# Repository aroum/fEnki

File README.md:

# fEnki  
fEnki is an open source (free) version of Enki (gbEnki).
fEnki is fully compatible with gbEnki. You can use gbEnki [cases, plates](https://github.com/aroum/gbEnki) and [firmware](https://github.com/aroum/zmk-gbEnki) on your fEnki.

Gerber files can be downloaded in the [releases section](https://github.com/aroum/fEnki/releases).

Actually, the photo is of gEnki, as soon as gEnki is assembled I will update the photo.

---

## Main Features:  
* 42/36 switches
* Easily accessible power switch and reset button 
* Bluetooth support
* 3 status LEDs
* Double sided board design
* Choc spacing

---
## BOM:  
### Electronic components:
| Component         | Model        | Qty (42-key) | Qty (36-key) |
| ----------------- | ------------ | ------------ | ------------ |
| Reset Button      | SMD 3x4x2mm  | 2            | 2            |
| MCU               | nice!nano v2 | 2            | 2            |
| Diodes            | 1N4148WS T4  | 42           | 36           |
| Power Switch      | BSI-10H      | 2            | 2            |
| Battery           | 301230       | 2            | 2            |
| LEDs              | SMD 0603     | 6            | 6            |
| Resistors         | 0603 1–10k   | 6            | 6            |
| Keyboard Switches | Choc v1      | 42           | 36           |
| Sockets           | PH3.5        |

### Mechanical parts:
| Component        | Model      | Qty (42-key) | Qty (36-key) |
| ---------------- | ---------- | ------------ | ------------ |
| PCBs             | 1.6        | 2            | 2            |
| Cover PCBs       | 0.8-1.6    | 2            | 2            |
| Spacers          | m2x8+      | 4            | 4            |
| Screws           | m2x4 T5*   | 12           | 12           |
| Screws           | m2x5 T5*   | 8            | 8            |
| Nuts             | m2         | 12           | 12           |
| Bumpons          | 5x2mm      | 14           | 14           |
| Magnets for case | disc 7x2mm | 8+           | 8+           |

 *If you are doing a plate assembly you need screws 1mm longer

 [IBOM](https://htmlpreview.github.io/?https://github.com/aroum/fEnki/blob/master/pcb/ibom.html)
---

## Assembly Instructions

### 1. Solder the Diodes

Solder all diodes except the thumb cluster diodes on the **top side** of the PCB. The thumb cluster diodes are slightly elevated and should be soldered on the **bottom side**.
All diodes must face the same direction: align the stripe on the diode body with the stripe on the PCB silkscreen (or with the round pad if the stripe is not visible).

### 2. Solder the LEDs

Solder the LEDs on the **top side** of the PCB.

### 3. Solder the Resistors

Solder resistors on the **bottom side** of the PCB. You can replace them later if you find the LEDs too bright.

### 4. Solder the Reset Button

Mount and solder the reset button on the **top side**.

### 5. Solder the Power Switch

Solder the toggle switch on the **top side**. It's recommended to solder the legs from both sides for durability. Clip off any excess legs.

### 6. Solder the Hotswap Sockets

Solder the sockets. Optionally, you can sand the socket edges for a cleaner look. Clip off any protruding legs.

### 7. Solder the Jumpers

Solder the jumpers on the **bottom side**, near the sockets and power switch. If you're struggling with this step, reduce the soldering temperature to around 200–250°C.

### 8. Solder the TRRS Jack (Optional)

Only if needed — mount and solder the TRRS connector.

### 9. Install and Solder the Microcontroller

Insert male pin headers into the sockets, place the microcontroller on top, clip the protruding legs, then solder.

### 10. Clean the Board

Remove the microcontroller and thoroughly clean the PCB.
If the reset button or switch is not working properly, apply isopropyl alcohol inside, click the button repeatedly, then blow it out.
At this point, you can test the circuit by shorting key pins with tweezers.

### 11. Solder the Switches

Mount and solder the switches. Clip off any protruding legs.
Optionally, screw in mounting screws and secure them with nuts. Depending on the switch model, screws may get slightly stuck between switches — this is generally not an issue.

### 12. Connect the Battery

Solder the battery, observing correct polarity. You can secure it with double-sided tape.

### 13. Final Cleaning

Do a final cleaning of the PCB.

### 14. Flash the Firmware and Bootloader

Flash the firmware. Flashing the bootloader is optional — it is only required to enable LED blinking during boot mode.

### 15. Assemble the Case

Screw the PCB into the case. Optionally, install magnets and rubber feet.
If nuts don’t fit into the slots, you can pre-thread them onto a screw, insert into the slot, heat with a soldering iron, then unscrew. If nuts are loose, use a small drop of super glue.

### 16. Attach Standoffs

Secure the standoffs to the case.

### 17. Attach the Cover

Mount and secure the case cover.

### 18. Install Keycaps

Place the keycaps onto the switches. Done!

---

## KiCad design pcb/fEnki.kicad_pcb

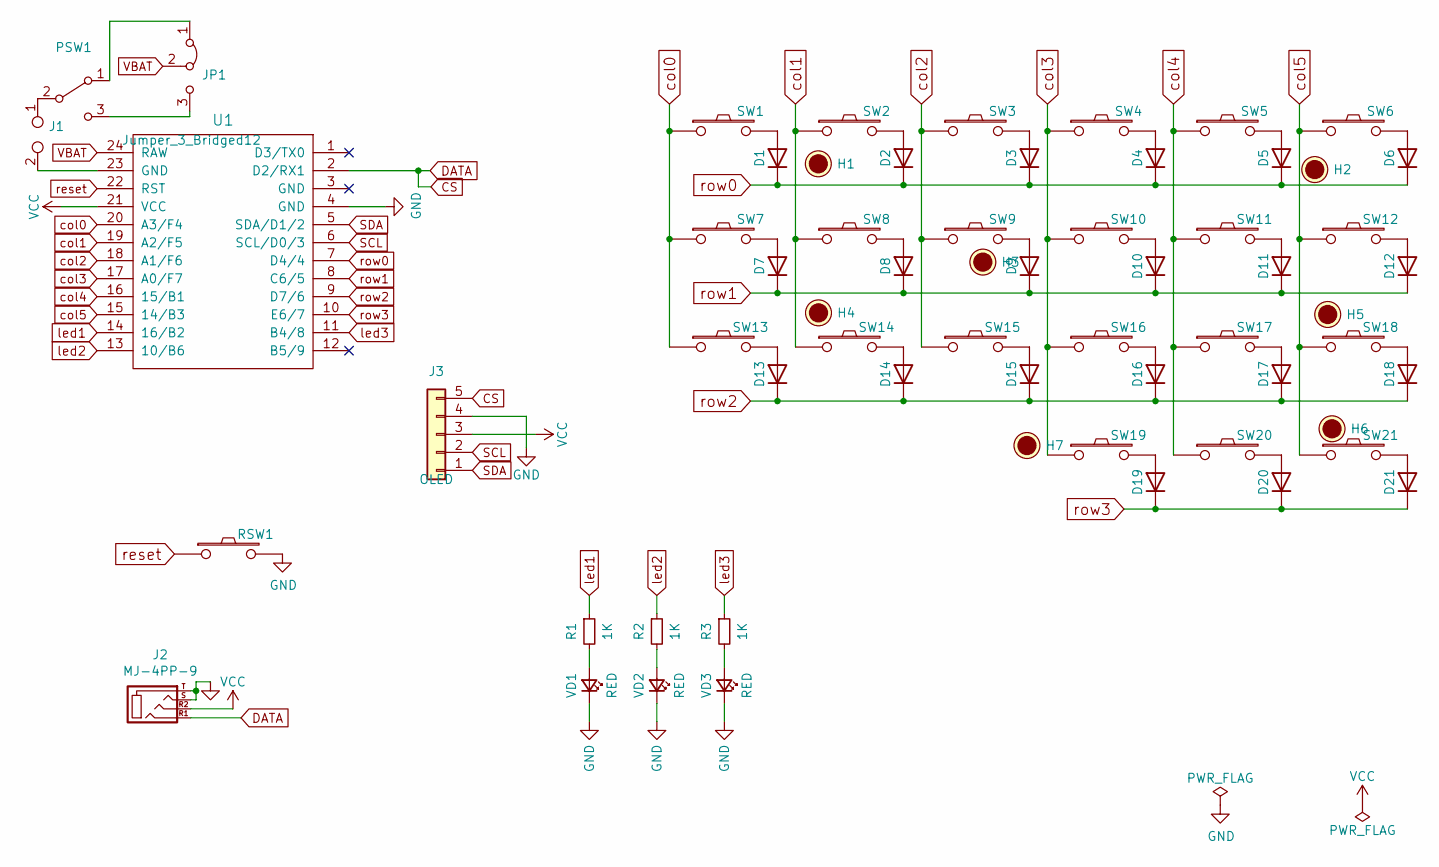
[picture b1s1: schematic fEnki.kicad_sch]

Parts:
D1, D2, D3, D4, D5, D6, D7, D8, D9, D10, D11, D12, D13, D14, D15, D16, D17, D18, D19, D20, D21: D; D_SOD-323_HandSoldering
H1, H2, H3, H4, H5, H6, H7: Hole; HOLE
J1: TestPoint_2Pole; battery_conn
J2: MJ-4PP-9; MJ-4PP-9_dual
J3: OLED; nice_view_1side
JP1: Jumper_3_Bridged12
PSW1: SW_SPDT; switch_MSK-12C02_smd
R1, R2, R3: 1K; R_0603_1608Metric_rev
RSW1: SW_PUSH; SW_3x4x2_2legs
SW1, SW2, SW3, SW4, SW5, SW6, SW7, SW8, SW9, SW10, SW11, SW12, SW13, SW14, SW15, SW16, SW17, SW18, SW19, SW20, SW21: SW_PUSH; ChocV1_topor
U1: ProMicro_r; ProMicro_v4
VD1, VD2, VD3: RED; LED_0603_1608Metric+1.8Е_THT_rev
logo1: Logo; Logo_Enki42_mini

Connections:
CS: J2.R1, J3.5, U1.2 (D2/RX1)
GND: J2.S, J2.T, J3.4, RSW1.2, U1.4 (GND), VD1.1 (K), VD2.1 (K), VD3.1 (K)
unnamed: D1.2 (A), SW1.2
unnamed: D2.2 (A), SW2.2
unnamed: D3.2 (A), SW3.2
unnamed: D4.2 (A), SW4.2
unnamed: D5.2 (A), SW5.2
unnamed: D6.2 (A), SW6.2
unnamed: D7.2 (A), SW7.2
unnamed: D8.2 (A), SW8.2
unnamed: D9.2 (A), SW9.2
unnamed: D10.2 (A), SW10.2
unnamed: D11.2 (A), SW11.2
unnamed: D12.2 (A), SW12.2
unnamed: D13.2 (A), SW13.2
unnamed: D14.2 (A), SW14.2
unnamed: D15.2 (A), SW15.2
unnamed: D16.2 (A), SW16.2
unnamed: D17.2 (A), SW17.2
unnamed: D18.2 (A), SW18.2
unnamed: D19.2 (A), SW19.2
unnamed: D20.2 (A), SW20.2
unnamed: D21.2 (A), SW21.2
unnamed: J1.2, U1.23 (GND)
unnamed: JP1.1 (A), PSW1.1 (A)
unnamed: JP1.3 (B), PSW1.3 (C)
unnamed: J1.1, PSW1.2 (B)
unnamed: R1.2, VD1.2 (A)
unnamed: R2.2, VD2.2 (A)
unnamed: R3.2, VD3.2 (A)
SCL: J3.2, U1.6 (SCL/D0/3)
SDA: J3.1, U1.5 (SDA/D1/2)
VBAT: JP1.2 (C), U1.24 (RAW)
VCC: J2.R2, J3.3, U1.21 (VCC)
col0: SW1.1, SW7.1, SW13.1, U1.20 (A3/F4)
col1: SW2.1, SW8.1, SW14.1, U1.19 (A2/F5)
col2: SW3.1, SW9.1, SW15.1, U1.18 (A1/F6)
col3: SW4.1, SW10.1, SW16.1, SW19.1, U1.17 (A0/F7)
col4: SW5.1, SW11.1, SW17.1, SW20.1, U1.16 (15/B1)
col5: SW6.1, SW12.1, SW18.1, SW21.1, U1.15 (14/B3)
led1: R1.1, U1.14 (16/B2)
led2: R2.1, U1.13 (10/B6)
led3: R3.1, U1.11 (B4/8)
reset: RSW1.1, U1.22 (RST)
row0: D1.1 (K), D2.1 (K), D3.1 (K), D4.1 (K), D5.1 (K), D6.1 (K), U1.7 (D4/4)
row1: D7.1 (K), D8.1 (K), D9.1 (K), D10.1 (K), D11.1 (K), D12.1 (K), U1.8 (C6/5)
row2: D13.1 (K), D14.1 (K), D15.1 (K), D16.1 (K), D17.1 (K), D18.1 (K), U1.9 (D7/6)
row3: D19.1 (K), D20.1 (K), D21.1 (K), U1.10 (E6/7)

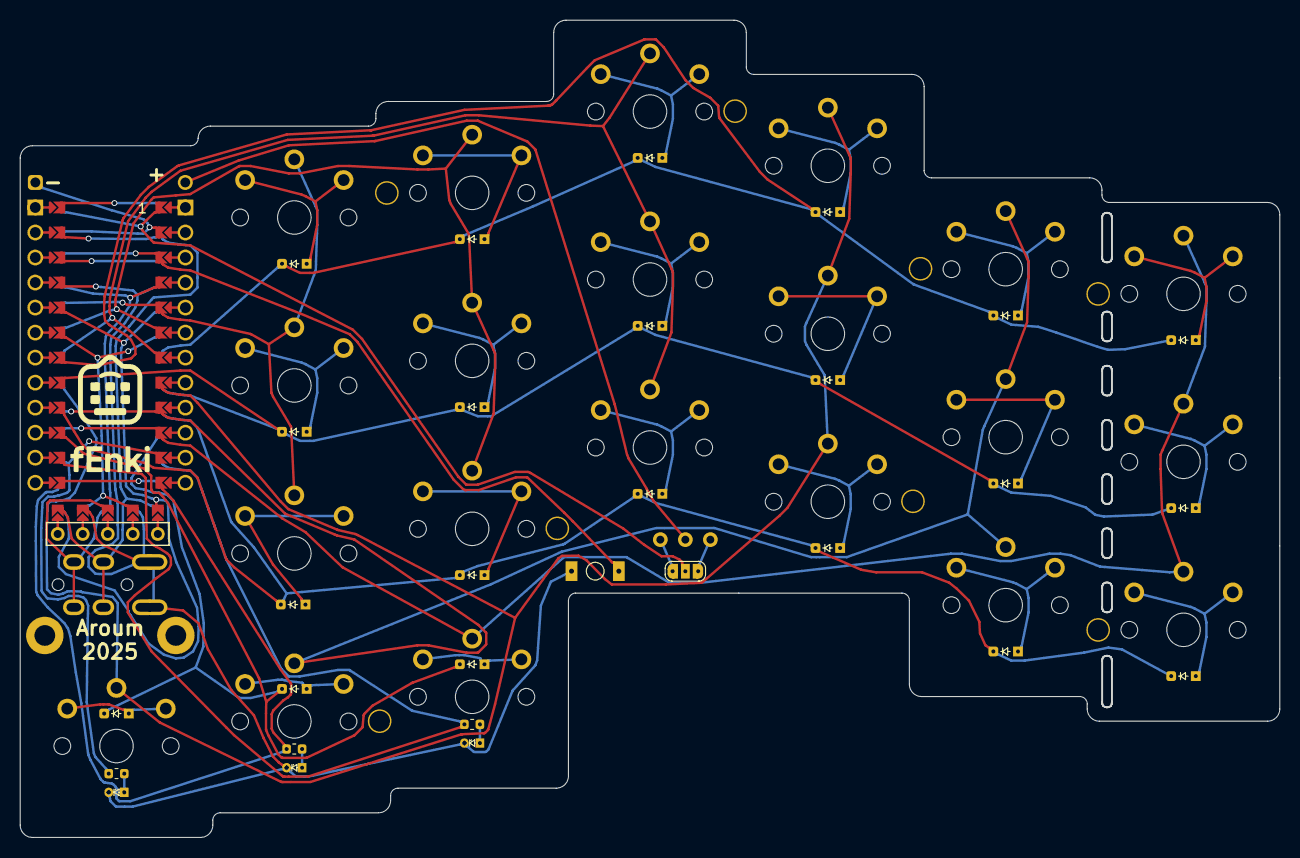
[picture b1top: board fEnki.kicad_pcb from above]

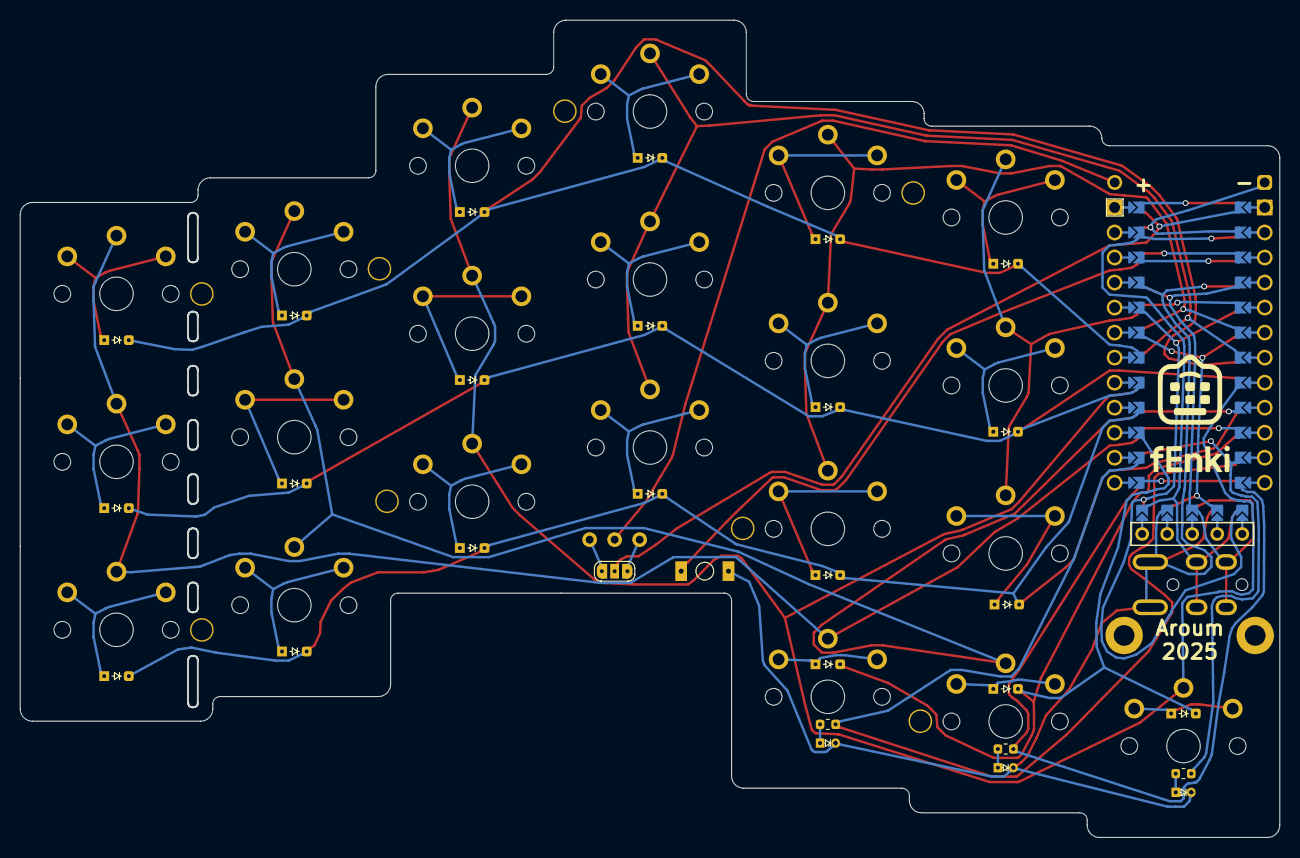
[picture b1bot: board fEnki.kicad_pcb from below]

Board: 2 copper layers, 127.8 x 82.9 mm, 76 parts (11 on the bottom side), 48 nets.

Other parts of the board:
G1, G1#2, G2, G2#2: LOGO
H8, H9, H10: Hole; HOLE
cut1, cut2, cut3, cut4, cut5, cut6, cut7: cutout_3

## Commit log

2025-05-08 init
